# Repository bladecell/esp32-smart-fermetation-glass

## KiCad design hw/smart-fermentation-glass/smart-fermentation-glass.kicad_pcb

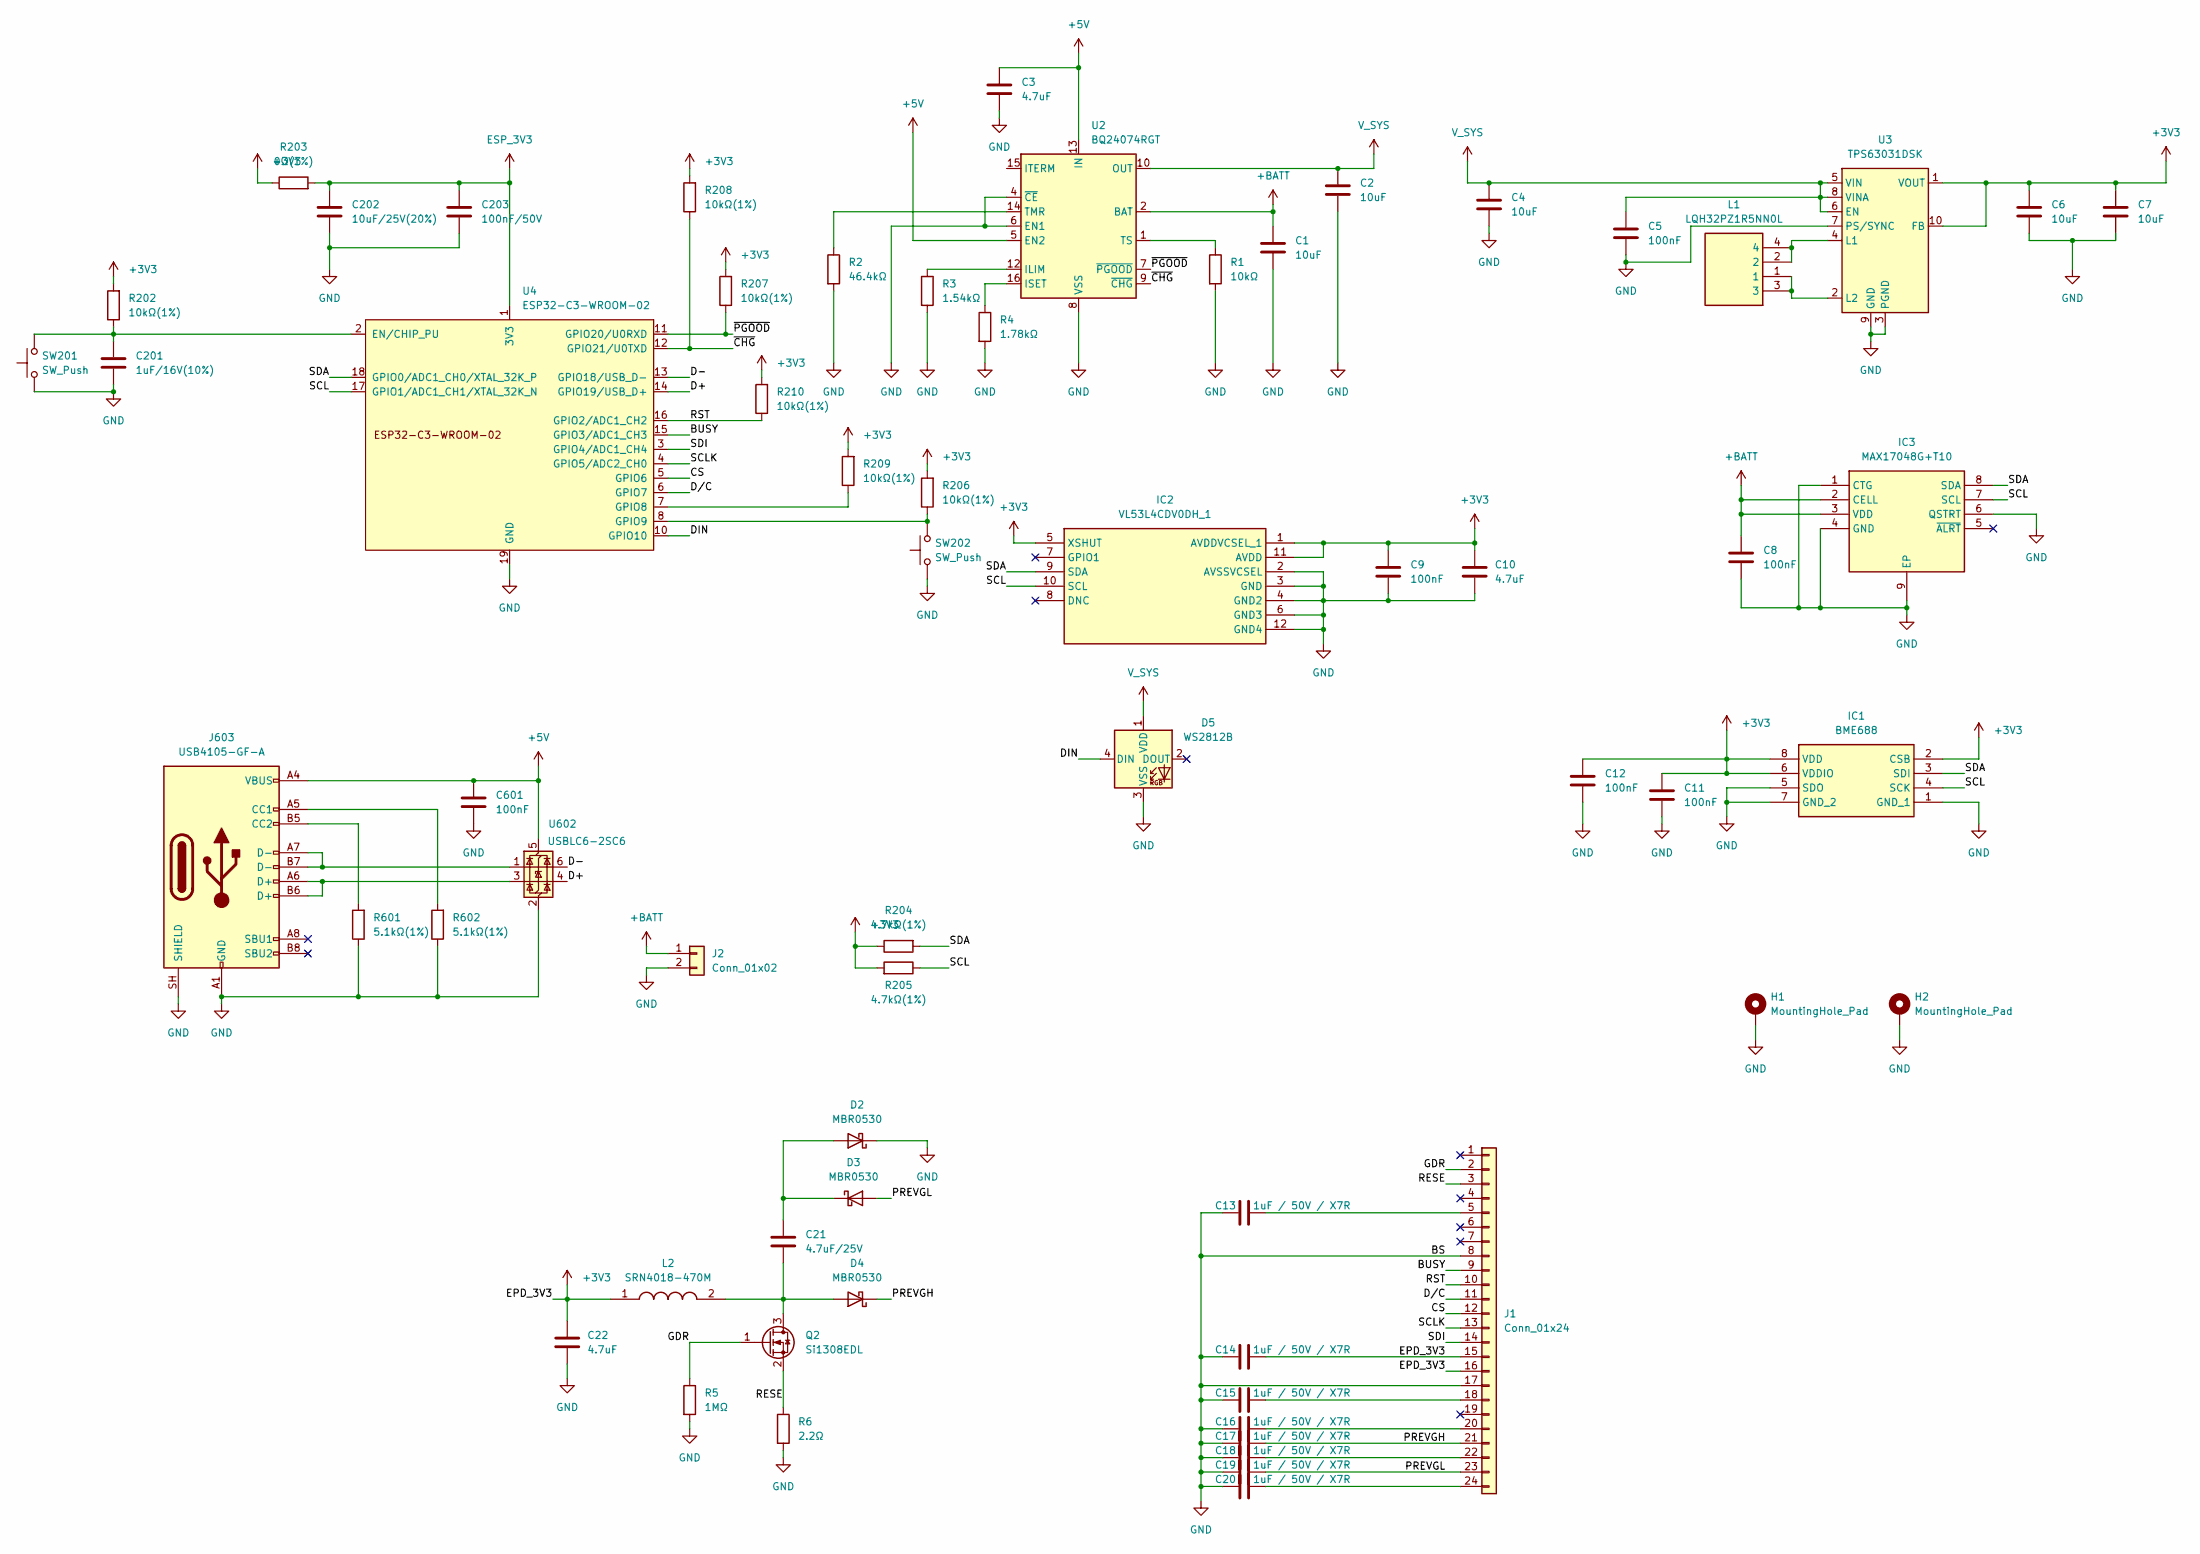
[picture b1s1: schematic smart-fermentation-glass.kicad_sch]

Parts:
C1, C2, C4, C6, C7: 10uF; C_0603_1608Metric; Mouser Part Number 81-GRM188R61E106MA3D
C3, C10, C22: 4.7uF; C_0603_1608Metric; Mouser Part Number 81-GRM188R61C475KE1D
C5, C8, C9, C11, C12, C601: 100nF; C_0603_1608Metric; Mouser Part Number 581-06035C104KAT2A
C13, C14, C15, C16, C17, C18, C19, C20: 1uF / 50V / X7R; C_0603_1608Metric; Mouser Part Number 581-06035C105KAT2A
C21: 4.7uF/25V; C_0805_2012Metric; Mouser Part Number 81-GRM188R61C475KE1D
C201: 1uF/16V(10%); C_0603_1608Metric; Mouser Part Number 810-C1608X7R1C105K
C202: 10uF/25V(20%); C_0603_1608Metric; Mouser Part Number 81-GRM188R61E106MA3D
C203: 100nF/50V; C_0603_1608Metric; Mouser Part Number 581-06035C104KAT2A
D2, D3, D4: MBR0530; D_SOD-123; Mouser Part Number 863-MBR0530T1G
D5: WS2812B; LED_WS2812B_PLCC4_5.0x5.0mm_P3.2mm
H1, H2: MountingHole_Pad; MountingHole_3.2mm_M3_ISO14580_Pad_TopBottom
IC1: BME688; Mouser Part Number 262-BME688
IC2: VL53L4CDV0DH_1; VL53L4CDV0DH1; Mouser Part Number 511-VL53L4CDV0DH/1
IC3: MAX17048G+T10; SON50P200X200X80-9N-D; Mouser Part Number 700-MAX17048G+T10
J1: Conn_01x24; Molex_502244-2430_1x24-1MP_P0.5mm_Horizontal; Mouser Part Number 538-502244-2430
J2: Conn_01x02; JST_PH_S2B-PH-K_1x02_P2.00mm_Horizontal; Mouser Part Number 306-S2BPHKSLFSNPP
J603: USB4105-GF-A; USB_C_Receptacle_GCT_USB4105-xx-A_16P_TopMnt_Horizontal; Mouser Part Number 640-USB4105-GF-A
L1: LQH32PZ1R5NN0L; LQH32CH100K53L; Mouser Part Number 81-LQH32PZ1R5NN0L
L2: SRN4018-470M; SRN4018470M; Mouser Part Number 652-SRN4018-470M
Q2: Si1308EDL; SOT-323_SC-70; Mouser Part Number 78-SI1308EDL-T1-GE3
R1: 10kΩ; R_0603_1608Metric; Mouser Part Number 603-RC0603FR-0710KL
R2: 46.4kΩ; R_0603_1608Metric; Mouser Part Number 603-RC0603FR-0746K4L
R3: 1.54kΩ; R_0603_1608Metric; Mouser Part Number 603-RC0603FR-071K54L
R4: 1.78kΩ; R_0603_1608Metric; Mouser Part Number 603-RC0603FR-071K78L
R5: 1MΩ; R_0603_1608Metric; Mouser Part Number 603-RC0603FR-071ML
R6: 2.2Ω; R_0603_1608Metric; Mouser Part Number 603-RC0603FR-072R2L
R202, R206, R207, R208, R209, R210: 10kΩ(1%); R_0603_1608Metric; Mouser Part Number 603-RC0603FR-0710KL
R203: 0Ω(1%); R_0603_1608Metric; Mouser Part Number 603-RC0603FR-070RL
R204, R205: 4.7kΩ(1%); R_0603_1608Metric; Mouser Part Number 603-RC0603FR-074K7L
R601, R602: 5.1kΩ(1%); R_0603_1608Metric; Mouser Part Number 603-RC0603FR-075K1L
SW201, SW202: SW_Push; SW_SPST_B3U-3000P; Mouser Part Number 653-B3U-3000P
U2: BQ24074RGT; VQFN-16-1EP_3x3mm_P0.5mm_EP1.6x1.6mm; Mouser Part Number 595-BQ24074RGTR
U3: TPS63031DSK; WSON-10-1EP_2.5x2.5mm_P0.5mm_EP1.2x2mm; Mouser Part Number 595-TPS63031DSKR
U4: ESP32-C3-WROOM-02; Mouser Part Number 356-ESP32C3WROOM02N4
U602: USBLC6-2SC6; SOT-23-6; Mouser Part Number 511-USBLC6-2SC6

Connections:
+3V3: C6.1, C7.1, C9.1, C10.1, C11.1, C12.1, C14.2, C22.1, IC1.2 (CSB), IC1.6 (VDDIO), IC1.8 (VDD), IC2.1 (AVDDVCSEL_1), IC2.5 (XSHUT), IC2.11 (AVDD), IC2.13 (AVDDVCSEL_2), J1.15, J1.16, L2.1, R202.2, R203.1, R204.1, R205.2, R206.2, R207.2, R208.2, R209.2, R210.2, U3.1 (VOUT), U3.10 (FB)
+5V: C3.1, C601.1, J603.A4 (VBUS), J603.A9 (VBUS), J603.B4 (VBUS), J603.B9 (VBUS), U2.5 (EN2), U2.13 (IN), U602.5 (VBUS)
+BATT: C1.1, C8.1, IC3.2 (CELL), IC3.3 (VDD), J2.1, U2.2 (BAT), U2.3 (BAT)
/BUSY: J1.9, U4.15 (GPIO3/ADC1_CH3)
/CS: J1.12, U4.5 (GPIO6)
/D+: U4.14 (GPIO19/USB_D+), U602.4 (I/O2)
/D-: U4.13 (GPIO18/USB_D-), U602.6 (I/O1)
/DIN: D5.4 (DIN), U4.10 (GPIO10)
/D/C: J1.11, U4.6 (GPIO7)
/GDR: J1.2, Q2.1 (G), R5.1
/PREVGH: C17.2, D4.1 (K), J1.21
/PREVGL: C19.2, D3.2 (A), J1.23
/RESE: J1.3, Q2.2 (S), R6.1
/RST: J1.10, R210.1, U4.16 (GPIO2/ADC1_CH2)
/SCL: IC1.4 (SCK), IC2.10 (SCL), IC3.7 (SCL), R205.1, U4.17 (GPIO1/ADC1_CH1/XTAL_32K_N)
/SCLK: J1.13, U4.4 (GPIO5/ADC2_CH0)
/SDA: IC1.3 (SDI), IC2.9 (SDA), IC3.8 (SDA), R204.2, U4.18 (GPIO0/ADC1_CH0/XTAL_32K_P)
/SDI: J1.14, U4.3 (GPIO4/ADC1_CH4)
/~CHG: R208.1, U2.9 (~CHG), U4.12 (GPIO21/U0TXD)
/~PGOOD: R207.1, U2.7 (~PGOOD), U4.11 (GPIO20/U0RXD)
ESP_3V3: C202.1, C203.1, R203.2, U4.1 (3V3)
GND: C1.2, C2.2, C3.2, C4.2, C5.2, C6.2, C7.2, C8.2, C9.2, C10.2, C11.2, C12.2, C13.1, C14.1, C15.1, C16.1, C17.1, C18.1, C19.1, C20.1, C22.2, C201.2, C202.2, C203.2, C601.2, D2.1 (K), D5.3 (VSS), H1.1 (1_1), H2.1 (1_1), IC1.1 (GND_1), IC1.5 (SDO), IC1.7 (GND_2), IC2.2 (AVSSVCSEL), IC2.3 (GND), IC2.4 (GND2), IC2.6 (GND3), IC2.12 (GND4), IC3.1 (CTG), IC3.4 (GND), IC3.6 (QSTRT), IC3.9 (EP), J1.8, J1.17, J2.2, J603.A1 (GND), J603.A12 (GND), J603.B1 (GND), J603.B12 (GND), J603.SH (SHIELD), R1.2, R2.2, R3.2, R4.2, R5.2, R6.2, R601.1, R602.1, SW201.1, SW202.1, U2.4 (~CE), U2.6 (EN1), U2.8 (VSS), U2.17 (VSS), U3.3 (PGND), U3.7 (PS/SYNC), U3.9 (GND), U3.11 (PGND), U4.9 (GND), U4.19 (GND), U602.2 (GND)
unnamed: C21.1, D2.2 (A), D3.1 (K)
unnamed: C21.2, D4.2 (A), L2.2, Q2.3 (D)
unnamed: C13.2, J1.5
unnamed: C15.2, J1.18
unnamed: C16.2, J1.20
unnamed: C18.2, J1.22
unnamed: C20.2, J1.24
unnamed: J603.A5 (CC1), R602.2
unnamed: J603.B5 (CC2), R601.2
unnamed: J603.A6 (D+), J603.B6 (D+), U602.3 (I/O2)
unnamed: J603.A7 (D-), J603.B7 (D-), U602.1 (I/O1)
unnamed: R3.1, U2.12 (ILIM)
unnamed: R4.1, U2.16 (ISET)
unnamed: R2.1, U2.14 (TMR)
unnamed: R1.1, U2.1 (TS)
unnamed: L1.2, L1.4, U3.4 (L1)
unnamed: L1.1, L1.3, U3.2 (L2)
unnamed: C201.1, R202.1, SW201.2, U4.2 (EN/CHIP_PU)
unnamed: R209.1, U4.7 (GPIO8)
unnamed: R206.1, SW202.2, U4.8 (GPIO9)
V_SYS: C2.1, C4.1, C5.1, D5.1 (VDD), U2.10 (OUT), U2.11 (OUT), U3.5 (VIN), U3.6 (EN), U3.8 (VINA)

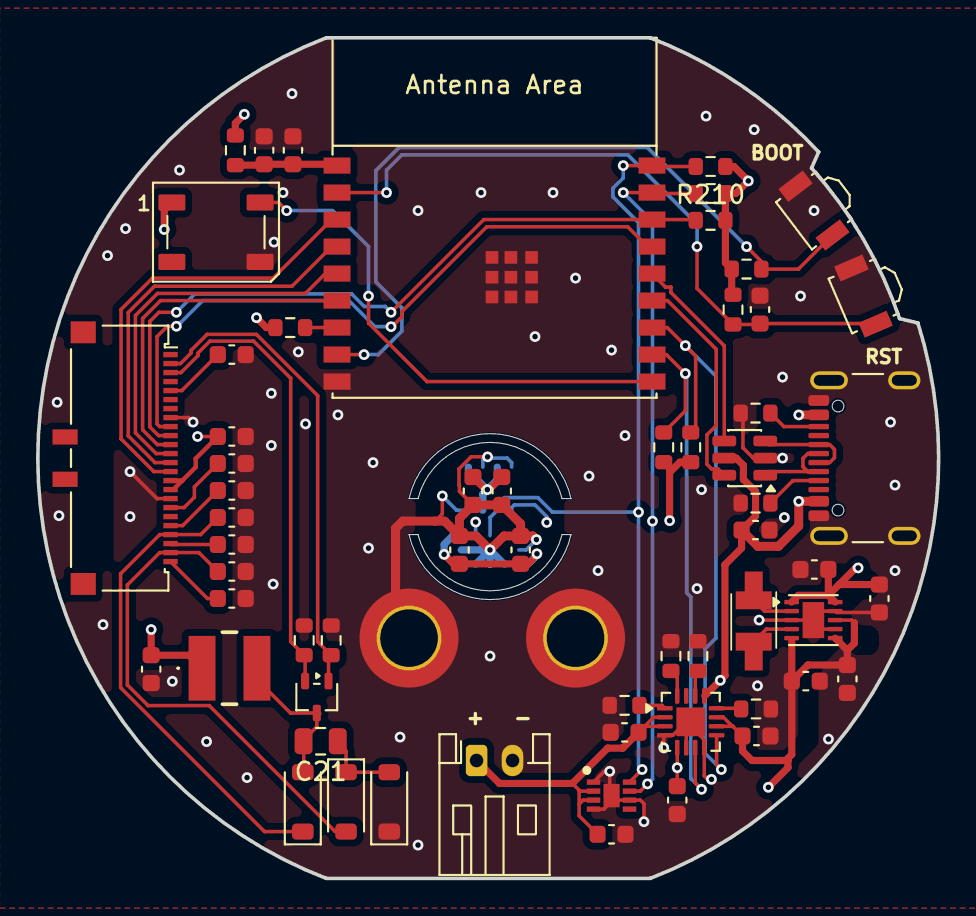
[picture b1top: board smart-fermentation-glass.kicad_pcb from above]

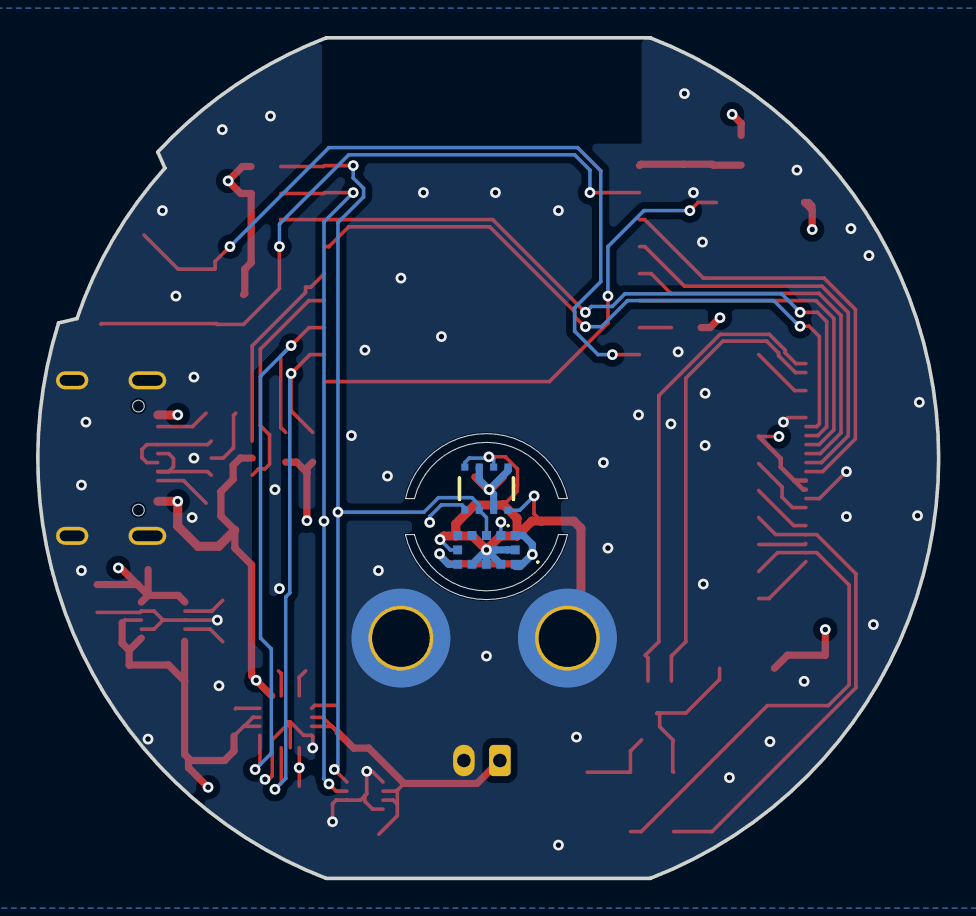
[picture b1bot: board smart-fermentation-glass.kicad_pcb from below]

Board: 4 copper layers, 50.0 x 46.7 mm, 64 parts (2 on the bottom side), 43 nets.
